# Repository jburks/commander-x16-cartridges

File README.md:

# Commander X16 Cartridges

## Overview

These are just prototype/practice designs for making a simple cartridge
for the Commander X16. They have not yet been tested on a real X16.

X16 Expansion and Cartridge footprints are available from:

https://github.com/jkominek/x16expansion

As a primer, cartridges can support up to 3.5MB of memory which can be a mix of RAM or ROM.
As an extension of the X16 ROM space, memory is divided into 16kb pages, 32 of which would
fit onto each memory chip. This assumes 8-bit 512k (4Mbit) memory chips are used.

Cartridges can also have I2C flash memory (for saving game states), and can use 
memory-mapped IO (MMIO) though it is *highly* recommended to use the `IO7`
address range as cartridges have been given priority to this range over expansion cards.

Cartridges are meant to be housed inside a Famicom style shell. They use the same edge connector
but are *NOT* compatible with the Famicon, NES, or any other system. **Do not attempt to plug 
an X16 cartridge into any other system than an X16 or visa-versa!**

Be aware that the "front" of the cartridge (the side which would have a typical label) is actually 
the back relative to a typical expansion card. This was done so that X16's which have a side cartridge 
slot can have the cartridge label side up. Cartridges and expansion cards use the same slots.

For more information, consult the x16-docs. 

## Chip Locations

Unless otherwise indicated, all cartridges are meant for booting directly from the cartridge.
This means the first chip (the one which is for ROM banks 32-63) will be a 512k ROM. Developers
that want their program to actually boot from ROM still need to setup the ROM image correctly.

For more information, consult the x16-docs.

## Cartridge Options

### SimpleCart

A no frills simple cartridge with a single ROM (512kb) and discrete decode logic that is inherited 
from the X16 Developer edition. This borrows some layout concepts from ROAM as made by Wavicle.
Big thanks to him for these contributions.

### ROAM (ROM + RAM)

Similar to the above but includes space for an SRAM chip (get it? ROM + RAM = ROAM) as well as an I2C NVRAM chip. 

The ROM is available in banks 32-63 and the RAM in banks 64-95. The banks can be 
swapped by cutting jumpers `JP3` and `JP4` and placing solder bridges over `JP2` and `JP5`.
That would place the RAM in banks 32-63 which can be beneficial when testing cartridge code.
The RAM can be loaded with cartridge data and then the X16 can be rebooted (leaving the 
data in place) which should boot off the RAM as if it were ROM.

The I2C NVRAM can store up to 8k (if using the chip provided in the BOM or one similar)
and can be useful for storing save data.

Huge thanks to Joe Burks (Wavicle) for handling a majority of the routing which has made for a 
gorgeous PCB layout and one that is also fairly easy to understand. Likewise he came up with
the solder-jumper options as well as the I2C additions and layout.

## Decode Explanation

The logic sections are derived fairly heavily from the X16 Dev 1.0 schematic.

`ROMB7-ROMB0` can be thought of as the ROM address lines. These are decoded from the
ROMBANK zeropage bank value (`$01`) by the X16 itself and are presented along the cartridge
connector.

We can take this 8-bit number and carve it up into chip select lines, which are `ROMB7-ROMB5`;
and additional address lines for the RAM/ROM chips, which as `ROMB4-ROMB0`.

Since each RAM/ROM has 512k of 8-bit memory, it means we can have up to 8 512k chips. 
The first chip is the System ROM for X16 (it is for banks 0-31) which means the rest
are available to cartridges.

| Banks (Decimal) | Banks (Hex) | ROMB7-ROMB5 (Binary) | Chip              |
| --------------- | ----------- | -------------------- | ----------------- |
| 00-31           | $00-$1F     | 000                  | 0 (System ROM)    |
| 32-63           | $20-$3F     | 001                  | 1 (Cart Boot)     | 
| 64-95           | $40-$5F     | 010                  | 2                 |
| 96-127          | $60-$7F     | 011                  | 3                 |
| 128-159         | $80-$9F     | 100                  | 3                 | 
| 160-191         | $A0-$BF     | 101                  | 3                 | 
| 192-223         | $C0-$DF     | 110                  | 3                 | 
| 224-256         | $E0-$FF     | 111                  | 3                 | 

### 74HCT138

This is known as a demux. It takes as input 3 signals (A0-A2) which represent 
numerical values 0-7 and enables only one of the output pins. These are used
as chip selects by taking the top 3 bits (`ROMB7-ROMB5` as noted above) as 
inputs for the demux.

Note that the System ROM is on the mainboard so the first output of the 138 
should not be used.

The outputs each go to the chip-select of a specific RAM or ROM to enable
that particular chip for the given bank range.

### 74HCT00

This is a 4 gate NAND IC. This is used to invert signals and provide a logical AND
function at the same time. For the cartridges it performs 2 functions:

#### ROM Enable

Not to be confused with chip-select, this ends up being the enable input to the 74HCT138
so that the outputs are enabled only when the X16 is reading or writing from the ROM
address space (`$C000-$FFFF`). In binary this is
`1100 0000 0000 0000 - 1111 1111 1111 1111`. That means the 2 topmost address lines 
(`A15-A14`) can be used as inputs to one of the NAND gates. Since the 74HCT138 uses
active-low (inverted) inputs, we provide this output to both the E0 and E1 pins 
of the 74HCT138.

#### Read / Write (PHI2 / RWB)

In this context, `PHI2` can be thought of as the system clock. `RWB` tell us if the 
CPU is doing a read or a write. We combine these together because `RWB` alone could result
in inconsistent read or writes because the 6502 does "work" outside of `PHI2`. It can be
roughly compared to modern DDR memory, where action happens on both the rising and falling
edges of a clock. We only care about the rising edge here.

So when PHI2 is high, a read or write may be taking place. To figure out which, `RWB` is used.
3 gates of the 74HCT00 are used to essentially provide a Write-Enable or Read-Enable line, 
noting that these are active low.

### Chip Address Lines

Because we are using 4Mbit RAM/ROM chips which are divided into 512k 8-bit bytes, each chip
has 19 address lines (`A18-A0`). 2^19 is 512k. The first 14 address lines (`A13-A0`) form
the lower address. Of note 2^14 is 16k which just so happens to be the bank page size.
The top addresses (`A18-A14`) are formed from the bottom 5 bits of the `ROMB` address space.
2^5 is 32, which is how many pages each chip can support.

As noted above, the top `ROMB` bits are used for chip selects and thus each ROM does not 
actually see those. Using bigger or smaller RAM or ROM chips would change how this works.

## Why 4-Layer and All the Ground VIAs?

Folks looking at the PCBs may wonder why the need for a 4-layer board and all those ground
VIAs? While it may not be strictly necessary at the 8 MHz speed the X16 runs at, timings
can be tricky and the parallel bus can add some complexity. The 4-layer board allows using
2 dedicated ground planes in an effort to avoid noise. Likewise the ground vias are so that
signals traveling from the top to the bottom layer have a ground return close by to minimize
the return travel to the nearest ground (and the nearest ground plane to the signal).

[This](https://www.youtube.com/watch?v=XD1jqFaA-uI) video explains things well.

While the 4-layer PCB adds a bit of cost (how much depends on the fab shop being used), it
simplifies ground wire routing and lowers noise. Since the fab shop used for making test
PCBs does not charge extra for more vias, the extra vias add zero cost while further lowering
noise.

## Bill of Materials

You can find the BOM in a LibreOffice .ODS formatted spreadsheet within the subdirectory
for each cartridge. This includes links to Mouser though most of these components are common
and should be found on Digikey and plenty of other places.

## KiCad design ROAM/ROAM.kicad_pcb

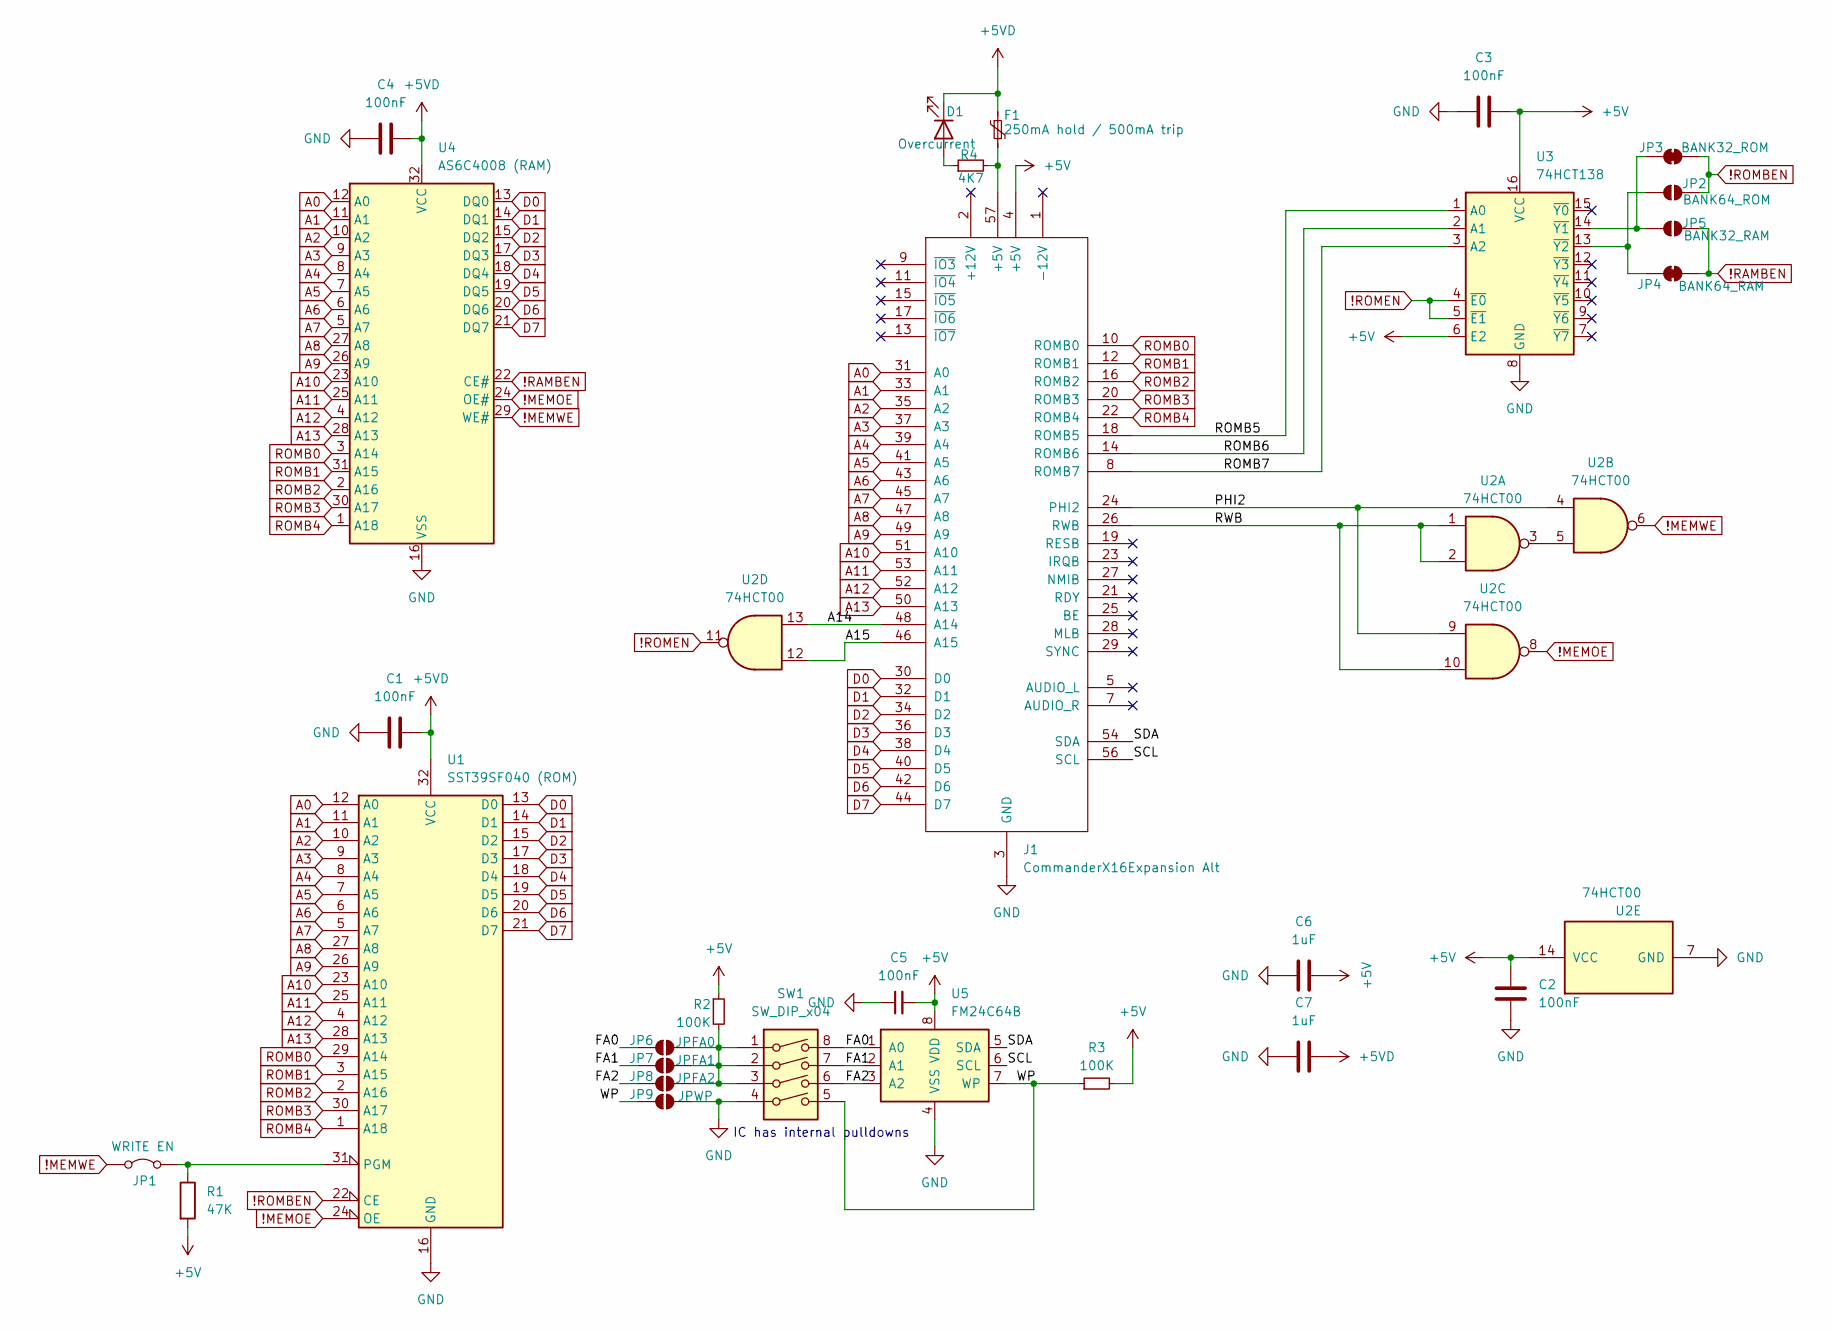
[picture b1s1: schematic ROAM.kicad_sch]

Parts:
C1, C2, C3, C4, C5: 100nF; C_Disc_D4.3mm_W1.9mm_P5.00mm
C6, C7: 1uF; C_Disc_D4.3mm_W1.9mm_P5.00mm
D1: Overcurrent; LED_D3.0mm
F1: 250mA hold / 500mA trip; Fuse_Bourns_MF-RHT100; MPN Littelfuse RXEF030S
J1: CommanderX16Expansion Alt; CommanderX16Cartridge
JP1: WRITE EN; TestPoint_2Pads_Pitch2.54mm_Drill0.8mm
JP2: BANK64_ROM; SolderJumper-2_P1.3mm_Open_TrianglePad1.0x1.5mm
JP3: BANK32_ROM; SolderJumper-2_P1.3mm_Bridged_Pad1.0x1.5mm
JP4: BANK64_RAM; SolderJumper-2_P1.3mm_Bridged_Pad1.0x1.5mm
JP5: BANK32_RAM; SolderJumper-2_P1.3mm_Open_TrianglePad1.0x1.5mm
JP6: JPFA0; SolderJumper-2_P1.3mm_Open_TrianglePad1.0x1.5mm
JP7: JPFA1; SolderJumper-2_P1.3mm_Open_TrianglePad1.0x1.5mm
JP8: JPFA2; SolderJumper-2_P1.3mm_Open_TrianglePad1.0x1.5mm
JP9: JPWP; SolderJumper-2_P1.3mm_Open_TrianglePad1.0x1.5mm
R1: 47K; R_Axial_DIN0204_L3.6mm_D1.6mm_P7.62mm_Horizontal
R2, R3: 100K; R_Axial_DIN0204_L3.6mm_D1.6mm_P7.62mm_Horizontal
R4: 4K7; R_Axial_DIN0204_L3.6mm_D1.6mm_P7.62mm_Horizontal
SW1: SW_DIP_x04; SW_DIP_SPSTx04_Slide_9.78x12.34mm_W7.62mm_P2.54mm; MPN Wurth 418117270904
U1: SST39SF040 (ROM); DIP_Socket-32_W11.9_W12.7_W15.24_W17.78_W18.5_3M_232-1285-0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; MPN Microchip SST39SF040-70-4C-PHE
U2: 74HCT00; DIP-14_W7.62mm; MPN TI SN74AHC00N
U3: 74HCT138; DIP-16_W7.62mm; MPN TI SN74AHC138N
U4: AS6C4008 (RAM); DIP-32_W15.24mm; MPN Alliance AS6C4008-55PCN
U5: FM24C64B; SOIC-8_3.9x4.9mm_P1.27mm; MPN Infineon FM24C64B-G

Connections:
!MEMOE: U1.24 (OE), U2.8, U4.24 (OE#)
!MEMWE: JP1.1 (A), U2.6, U4.29 (WE#)
!RAMBEN: JP4.2 (B), JP5.1 (A), U4.22 (CE#)
!ROMBEN: JP2.1 (A), JP3.2 (B), U1.22 (CE)
!ROMEN: U2.11, U3.4 (~E0), U3.5 (~E1)
+5V: C2.2, C3.1, C5.2, C6.2, J1.4 (+5V), R1.2, R2.1, R3.2, U2.14 (VCC), U3.6 (E2), U3.16 (VCC), U5.8 (VDD)
+5VD: C1.2, C4.2, C7.2, D1.1 (K), F1.1, U1.32 (VCC), U4.32 (VCC)
/A14: J1.48 (A14), U2.13
/A15: J1.46 (A15), U2.12
/FA0: JP6.2 (B), SW1.8, U5.1 (A0)
/FA1: JP7.2 (B), SW1.7, U5.2 (A1)
/FA2: JP8.2 (B), SW1.6, U5.3 (A2)
/PHI2: J1.24 (PHI2), U2.4, U2.9
/ROMB5: J1.18 (ROMB5), U3.1 (A0)
/ROMB6: J1.14 (ROMB6), U3.2 (A1)
/ROMB7: J1.8 (ROMB7), U3.3 (A2)
/RWB: J1.26 (RWB), U2.1, U2.2, U2.10
/SCL: J1.56 (SCL), U5.6 (SCL)
/SDA: J1.54 (SDA), U5.5 (SDA)
/WP: JP9.2 (B), R3.1, SW1.5, U5.7 (WP)
A0: J1.31 (A0), U1.12 (A0), U4.12 (A0)
A1: J1.33 (A1), U1.11 (A1), U4.11 (A1)
A2: J1.35 (A2), U1.10 (A2), U4.10 (A2)
A3: J1.37 (A3), U1.9 (A3), U4.9 (A3)
A4: J1.39 (A4), U1.8 (A4), U4.8 (A4)
A5: J1.41 (A5), U1.7 (A5), U4.7 (A5)
A6: J1.43 (A6), U1.6 (A6), U4.6 (A6)
A7: J1.45 (A7), U1.5 (A7), U4.5 (A7)
A8: J1.47 (A8), U1.27 (A8), U4.27 (A8)
A9: J1.49 (A9), U1.26 (A9), U4.26 (A9)
A10: J1.51 (A10), U1.23 (A10), U4.23 (A10)
A11: J1.53 (A11), U1.25 (A11), U4.25 (A11)
A12: J1.52 (A12), U1.4 (A12), U4.4 (A12)
A13: J1.50 (A13), U1.28 (A13), U4.28 (A13)
D0: J1.30 (D0), U1.13 (D0), U4.13 (DQ0)
D1: J1.32 (D1), U1.14 (D1), U4.14 (DQ1)
D2: J1.34 (D2), U1.15 (D2), U4.15 (DQ2)
D3: J1.36 (D3), U1.17 (D3), U4.17 (DQ3)
D4: J1.38 (D4), U1.18 (D4), U4.18 (DQ4)
D5: J1.40 (D5), U1.19 (D5), U4.19 (DQ5)
D6: J1.42 (D6), U1.20 (D6), U4.20 (DQ6)
D7: J1.44 (D7), U1.21 (D7), U4.21 (DQ7)
GND: C1.1, C2.1, C3.2, C4.1, C5.1, C6.1, C7.1, J1.3 (GND), J1.6 (GND), J1.55 (GND), J1.58 (GND), JP9.1 (A), SW1.4, U1.16 (GND), U2.7 (GND), U3.8 (GND), U4.16 (VSS), U5.4 (VSS)
unnamed: D1.2 (A), R4.1
unnamed: F1.2, J1.57 (+5V), R4.2
unnamed: JP1.2 (B), R1.1, U1.31 (PGM)
unnamed: JP2.2 (B), JP4.1 (A), U3.13 (~Y2)
unnamed: JP3.1 (A), JP5.2 (B), U3.14 (~Y1)
unnamed: JP6.1 (A), JP7.1 (A), JP8.1 (A), R2.2, SW1.1, SW1.2, SW1.3
unnamed: U2.3, U2.5
ROMB0: J1.10 (ROMB0), U1.29 (A14), U4.3 (A14)
ROMB1: J1.12 (ROMB1), U1.3 (A15), U4.31 (A15)
ROMB2: J1.16 (ROMB2), U1.2 (A16), U4.2 (A16)
ROMB3: J1.20 (ROMB3), U1.30 (A17), U4.30 (A17)
ROMB4: J1.22 (ROMB4), U1.1 (A18), U4.1 (A18)

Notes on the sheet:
IC has internal pulldowns

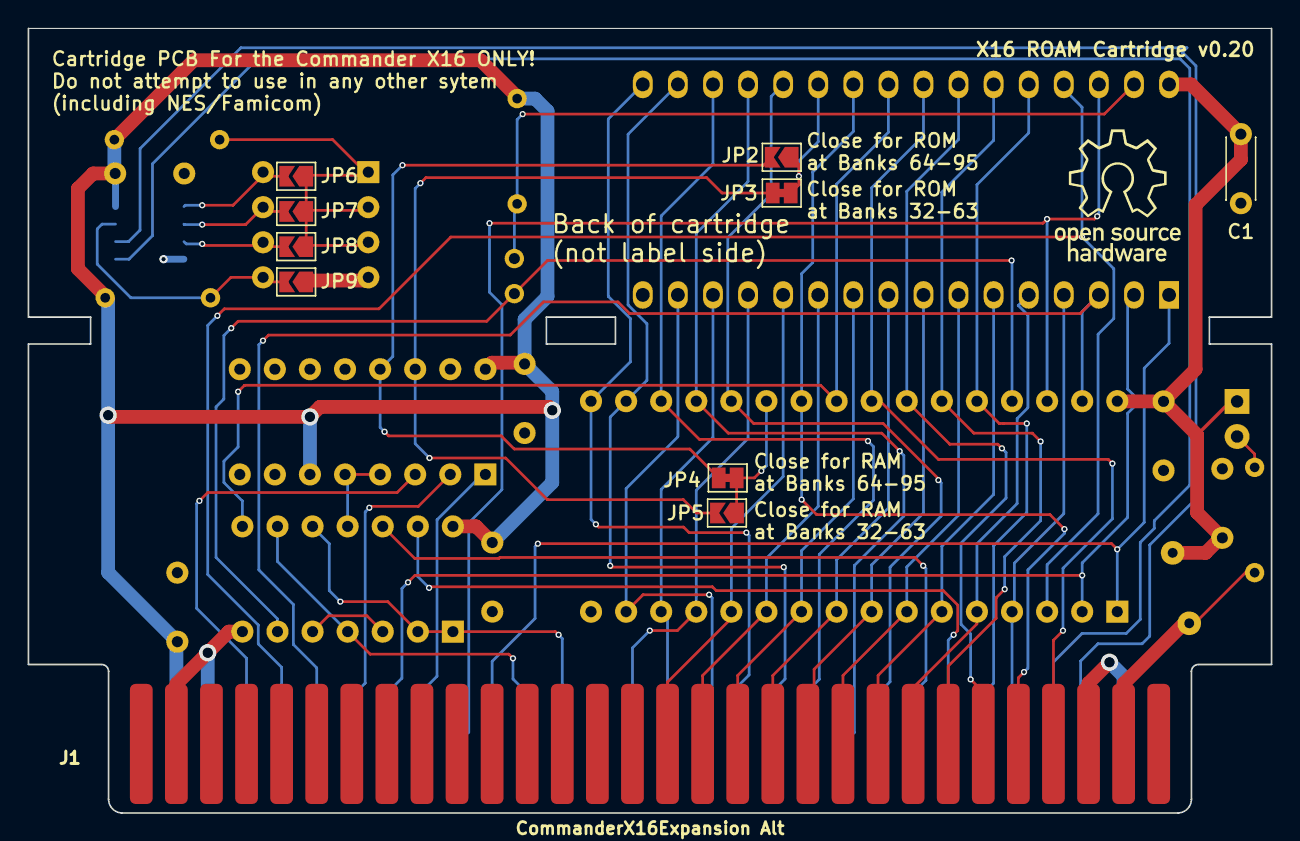
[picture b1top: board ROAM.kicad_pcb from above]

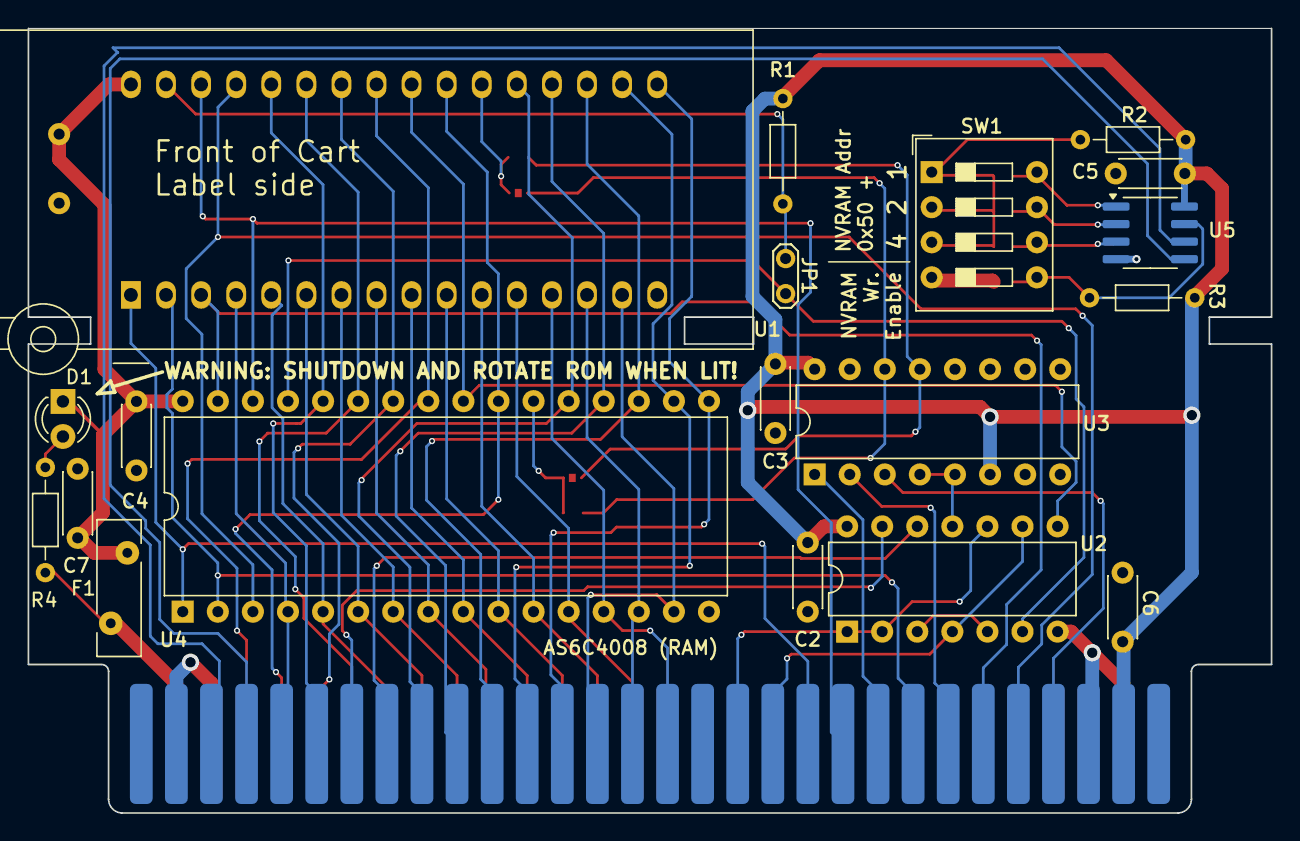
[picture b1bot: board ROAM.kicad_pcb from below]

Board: 4 copper layers, 90.0 x 56.8 mm, 29 parts (19 on the bottom side), 55 nets.

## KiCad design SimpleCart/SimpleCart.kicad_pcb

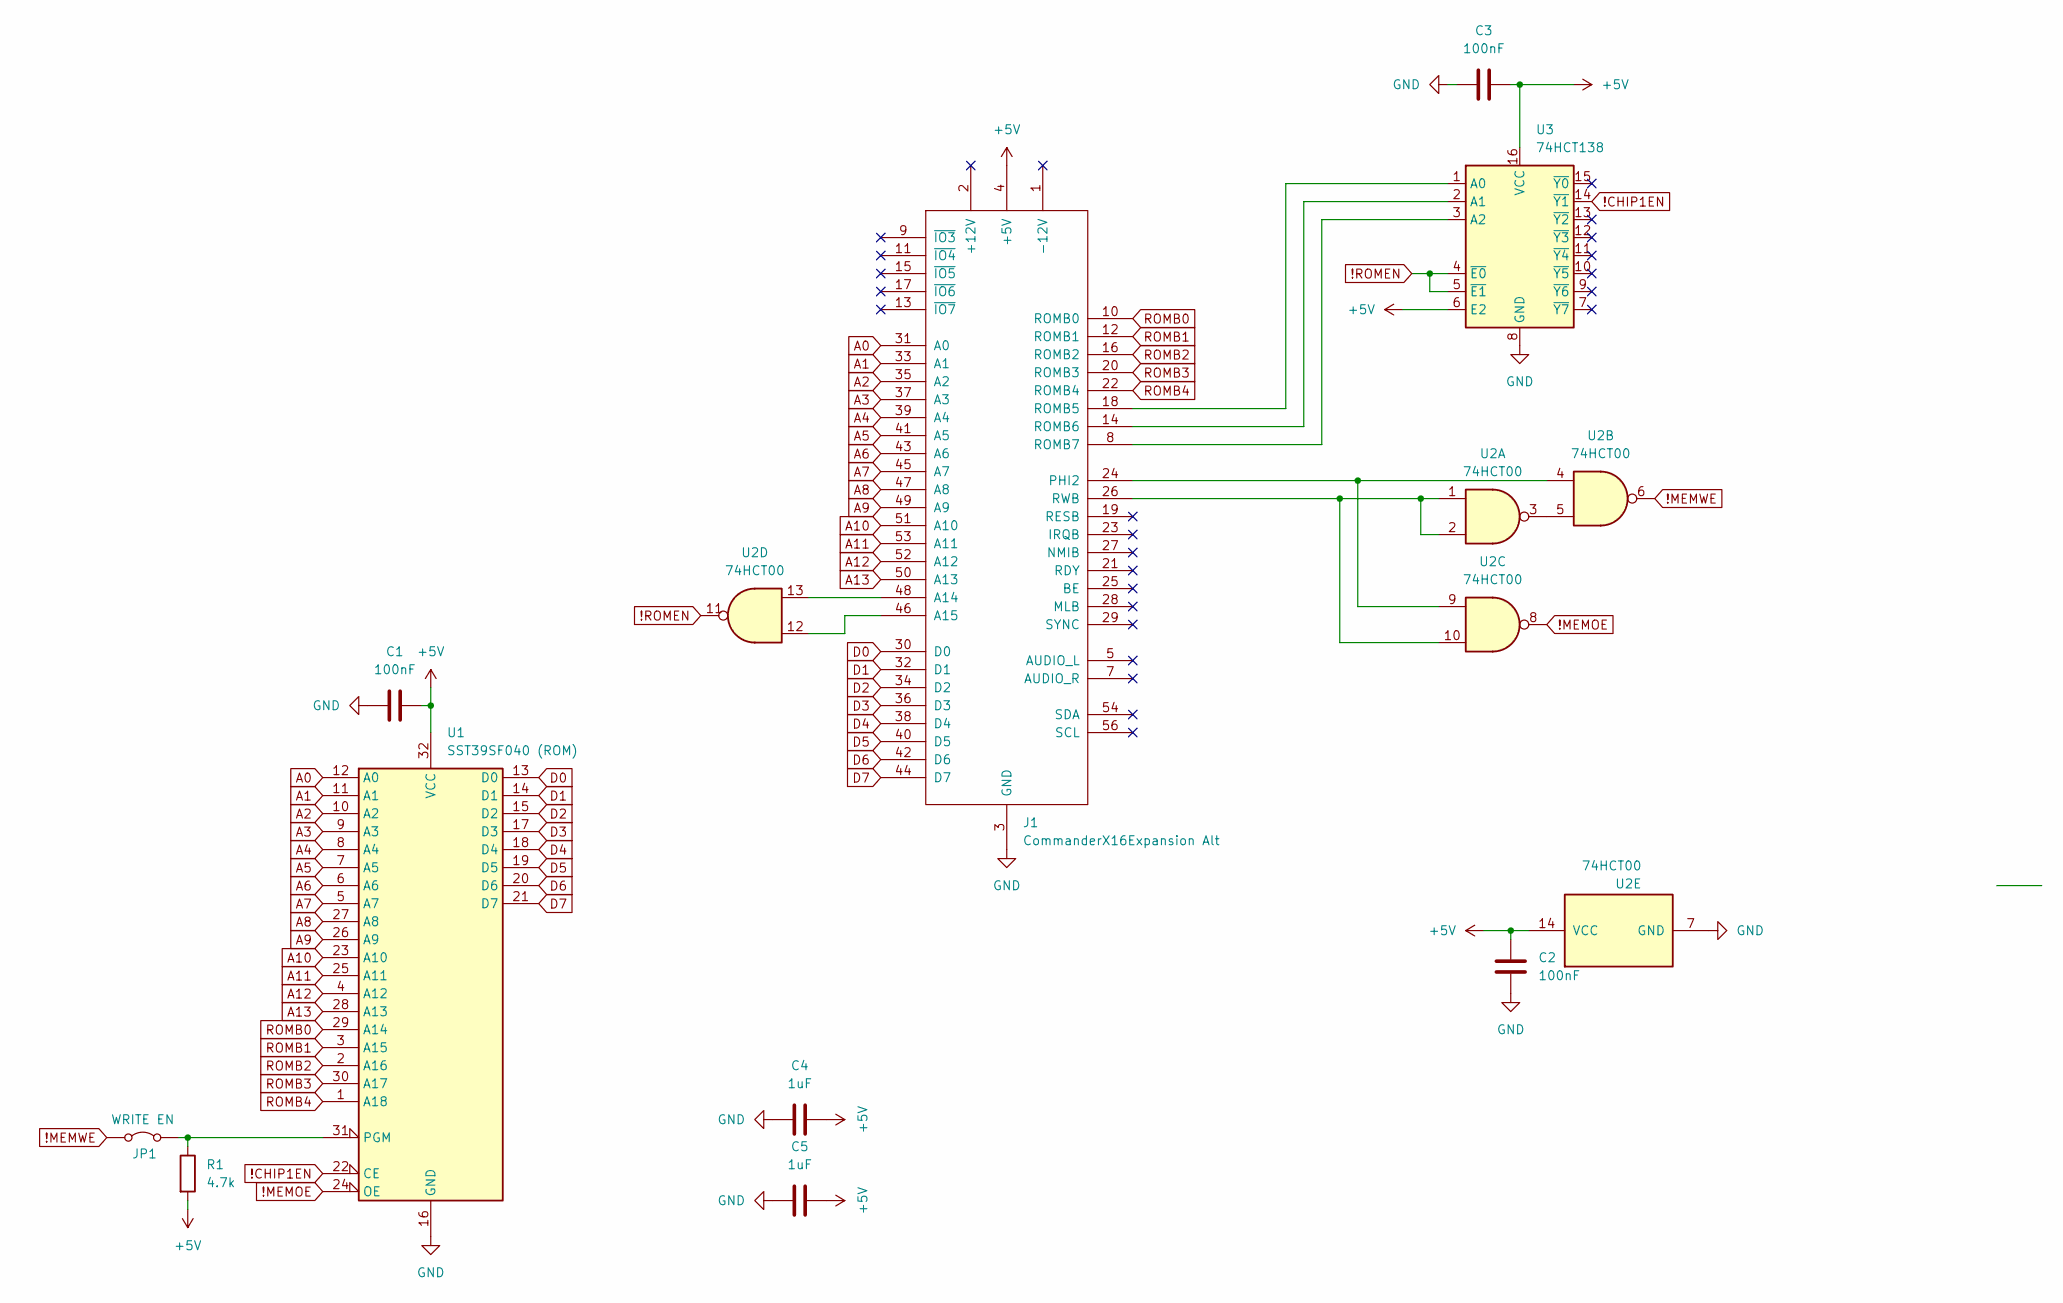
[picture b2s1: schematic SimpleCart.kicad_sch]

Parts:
C1, C2, C3: 100nF; C_Disc_D4.3mm_W1.9mm_P5.00mm
C4, C5: 1uF; C_Disc_D4.3mm_W1.9mm_P5.00mm
J1: CommanderX16Expansion Alt; CommanderX16SimpleCartridge
JP1: WRITE EN; TestPoint_2Pads_Pitch2.54mm_Drill0.8mm
R1: 4.7k; R_Axial_DIN0204_L3.6mm_D1.6mm_P7.62mm_Horizontal
U1: SST39SF040 (ROM); DIP-32_W15.24mm_Socket
U2: 74HCT00; DIP-14_W7.62mm_Socket
U3: 74HCT138; DIP-16_W7.62mm_Socket

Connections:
!CHIP1EN: U1.22 (CE), U3.14 (~Y1)
!MEMOE: U1.24 (OE), U2.8
!MEMWE: JP1.1 (A), U2.6
!ROMEN: U2.11, U3.4 (~E0), U3.5 (~E1)
+5V: C1.2, C2.2, C3.1, C4.2, C5.2, J1.4 (+5V), J1.57 (+5V), R1.2, U1.32 (VCC), U2.14 (VCC), U3.6 (E2), U3.16 (VCC)
A0: J1.31 (A0), U1.12 (A0)
A1: J1.33 (A1), U1.11 (A1)
A2: J1.35 (A2), U1.10 (A2)
A3: J1.37 (A3), U1.9 (A3)
A4: J1.39 (A4), U1.8 (A4)
A5: J1.41 (A5), U1.7 (A5)
A6: J1.43 (A6), U1.6 (A6)
A7: J1.45 (A7), U1.5 (A7)
A8: J1.47 (A8), U1.27 (A8)
A9: J1.49 (A9), U1.26 (A9)
A10: J1.51 (A10), U1.23 (A10)
A11: J1.53 (A11), U1.25 (A11)
A12: J1.52 (A12), U1.4 (A12)
A13: J1.50 (A13), U1.28 (A13)
D0: J1.30 (D0), U1.13 (D0)
D1: J1.32 (D1), U1.14 (D1)
D2: J1.34 (D2), U1.15 (D2)
D3: J1.36 (D3), U1.17 (D3)
D4: J1.38 (D4), U1.18 (D4)
D5: J1.40 (D5), U1.19 (D5)
D6: J1.42 (D6), U1.20 (D6)
D7: J1.44 (D7), U1.21 (D7)
GND: C1.1, C2.1, C3.2, C4.1, C5.1, J1.3 (GND), J1.6 (GND), J1.55 (GND), J1.58 (GND), U1.16 (GND), U2.7 (GND), U3.8 (GND)
unnamed: J1.48 (A14), U2.13
unnamed: J1.46 (A15), U2.12
unnamed: J1.24 (PHI2), U2.4, U2.9
unnamed: J1.18 (ROMB5), U3.1 (A0)
unnamed: J1.14 (ROMB6), U3.2 (A1)
unnamed: J1.8 (ROMB7), U3.3 (A2)
unnamed: J1.26 (RWB), U2.1, U2.2, U2.10
unnamed: JP1.2 (B), R1.1, U1.31 (PGM)
unnamed: U2.3, U2.5
ROMB0: J1.10 (ROMB0), U1.29 (A14)
ROMB1: J1.12 (ROMB1), U1.3 (A15)
ROMB2: J1.16 (ROMB2), U1.2 (A16)
ROMB3: J1.20 (ROMB3), U1.30 (A17)
ROMB4: J1.22 (ROMB4), U1.1 (A18)

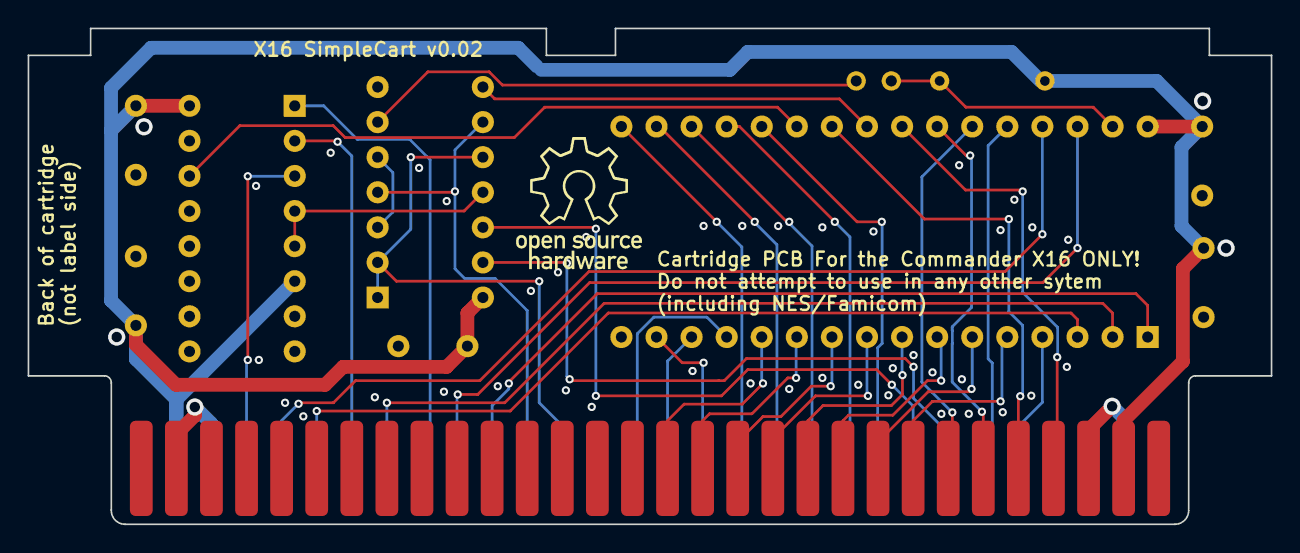
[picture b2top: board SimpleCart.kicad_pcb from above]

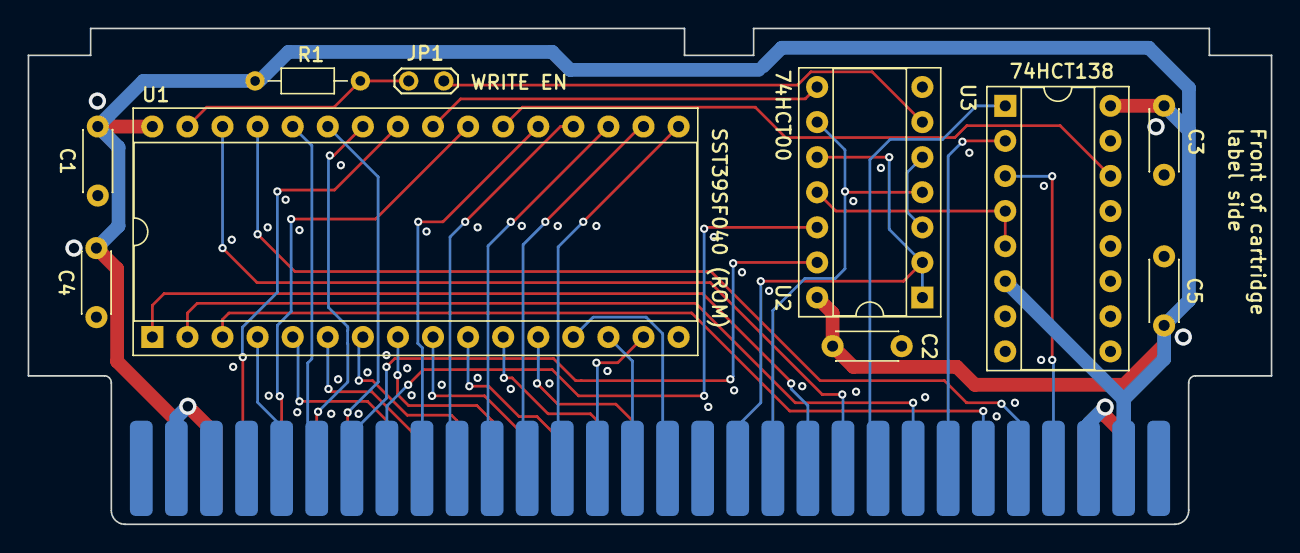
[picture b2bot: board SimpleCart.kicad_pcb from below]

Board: 4 copper layers, 90.0 x 35.9 mm, 11 parts (10 on the bottom side), 42 nets.

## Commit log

2024-09-30 Cleanup extra shiz
2024-09-30 Ignore backups and ZIPs
2024-09-30 Verification, changes
2024-09-30 Flip the board
2024-09-30 Routing yikes
2024-10-01 Routing madness
2024-10-01 BOM, fully routed
2024-10-01 Polish and a readme explaining WTF
2024-10-01 More tweaks
2024-10-01 Version #
2024-10-01 Safe commit
2024-10-01 Two layer routing with copper pours
2024-10-01 merged Wav's changes, minor routing changes, ROAM rename
2024-10-01 Removed references to me and the synth store
    Since the project now has other contributors I didn't feel right
    comandeering the silkscreen with my logo
2024-10-01 ROAM bom
2024-10-01 Added I2C NVRAM
2024-10-01 Add NVRAM, add edge connector sym/fp to proj
2024-10-02 Merged Wavicle's contributions to ROAM, added silk and some markup, updated readmed
2024-10-02 Updated ROAM BOM
2024-10-02 Add jumpers to swap RAM/ROM
2024-10-02 Silk
2024-10-02 Rounded connector edges; switched caps; NVRAM addr solder jumpers
2024-10-02 Cleaned up NVRAM Addr text
2024-10-02 Ported over Wavicle's latest changes
2024-10-02 credit where credit due
2024-10-02 Add parts
2024-10-02 Added label about pull-downs, updates to readme
2024-10-02 Tweaks to both Simplecart and ROAM
2024-10-02 Shoutout to Joe
2024-10-02 1uF Caps
2024-10-02 Images for readme
2024-10-02 Moar images
2024-10-02 Minor PCB updates, BOM
2024-10-02 Time to buy!
2024-10-04 Improved ground handling
2024-10-04 Ground vias
2024-10-04 Laying the ground work (har har)
2024-10-04 Added explanation of grounds to the readme
2024-10-04 Updated images
2024-10-04 Note about cart shells
2024-11-01 Routed new layout with larger footprint keepout zones.
2024-12-02 Add ROM reverse polarity circuit; Gerber out 0.20
